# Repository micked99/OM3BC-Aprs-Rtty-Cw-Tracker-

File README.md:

# OM3BC-Aprs-Rtty-Cw-Tracker-
OM3BC Aprs-Rtty-Cw Tracker 
OM3BC tracker info
Some extended information about the OM3BC tracker found here: www.om3bc.com/docs/payload/payload_en

Some extended information about the OM3BC tracker found here: www.om3bc.com/docs/payload/payload_en
My aim of the Eagle files is to make an as simple to build, cheap and light tracker as possible, a fully assambled board should weigh in on about 1 - 1.3gram,
a fully assambled board with solar cells and antenna about 3.5gram

Im using 6 of the smallest avalible (19x39mm) solar cells in series to power the board, it makes it run from and to 15-19° solar angle depending on Gps used

After more then 25 launches over the years and probably more then 10 pcb revisions I have come to this final? design, the intention of this page is to ease the building and configuring the OM3BC APRS / RTTY / CW tracker.

The rar file below contains all files mentioned in this small writeup

There are two different firmware versions depending on what Gps module you intend to use:

fw7.5 should be used with Ublox Max modules, I have so far only tested the Max7q and Max7c both working well,
the low voltage "c" version getting a bit longer "runtime" due to its lower voltage demands, Max 6 & 8 should work just as well.

fw14 should be used with ATGM336 Gps which is a "new" cheap module that can be found for around $3 on Aliexpress,
there is no flightmode that needs to be set on this module, it have been tested to over 32000m at the time of this write up.

You will also find Eagle pcb files in the rar for two types of PIC ic footprints.

I have tested both the L version and LF version of the PIC but could not see any advantages using the low voltage (LF) version of the ic

All versions of the si4x6x I have tried have worked well, so far I have tested SI4060, 4463 and 4063.

THE MOST important setting to get reliable startup of the board is to enable the Watch Dog Timer (WDT) you set all as 1:s as in the below picture.
To do this you press the "Configuration:" in the PICkit3 before you program the board.

You can read about the fuses in the pic18f26k22.pdf (rar)

Schematic

Settings Im using:
MYC SA6BSS-9
DEVIATION 425
POUT 8 (pout 100 using 4060 // pout 8 = 25mW on a 4x63)
APRS on
HOLD 2
TAIL on 2
INTEMP yes REF 19199985
UBLOX on (=atgm336)
TTEXT RTTY 434.5/100b7n2 Temp:\W Gps:\B
UNPROTO APRS V wide0-0 // = to not use digipeaters, leave unchanged if you want to use digipeaters
RFRQ 434500000 // putting the rtty up in ism band

Im using Termite terminal to setup the board, this as well as well as the PICkit3 is in the rar, termite also supports macros so you dont have to enter every setting everytime you setup a new board.

When you configure the board you have to use a rs232 programmer, the only one so far that works reliably is this type, look for it on ebay or aliexpress,
should cost arround 3-5$, note the DC jack, electrolytic caps and LEDs
The voltage out from this is 5V, to reduce this you can put 2 diods in series on the VCC to lower the voltage to more reasonable levels, or preferably a 3.3V LDO.

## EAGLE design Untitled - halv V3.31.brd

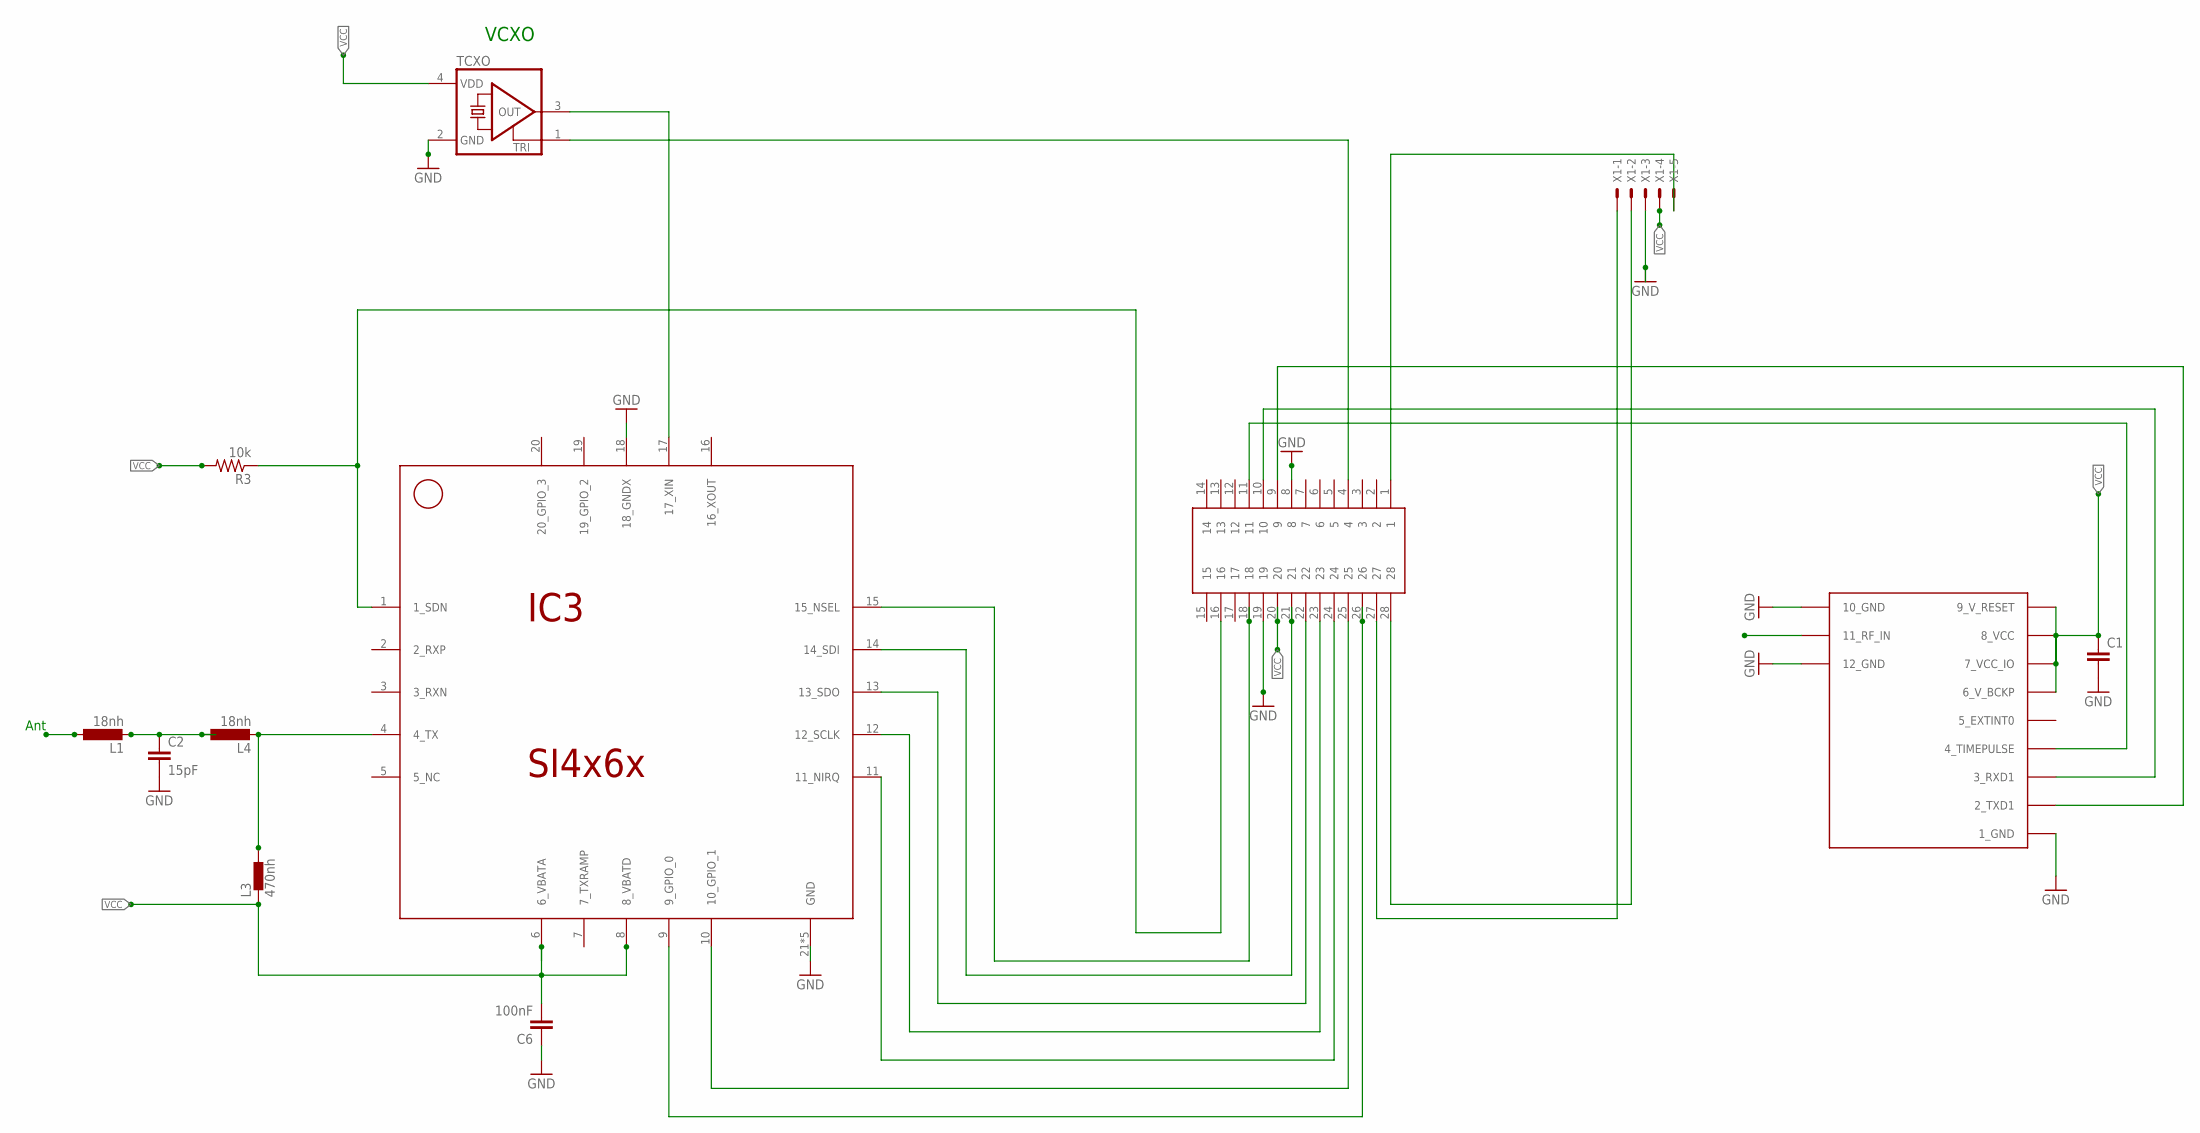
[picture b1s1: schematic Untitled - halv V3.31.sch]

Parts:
C1: CC0603; C0603
C2: 15pF; C0603K
C6: 100nF; C0402
IC3: SI4x6x; QFN-20
L1, L4: 18nh; L2012C
L3: 470nh; 0402
PIC-VERS3.3: SSOP28; SSOP28DB
R3: 10k; R0402
TCXO: CRYSTAL_3.2X2.5-TCXO
U$1: UBLOX_MAX
X1: 22-23-2051

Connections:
ANT: U$1.11_RF_IN
GND: C1.2, C2.2, C6.1, IC3.18 (18_GNDX), IC3.21 (GND), IC3.22 (GND), IC3.23 (GND), IC3.24 (GND), IC3.25 (GND), PIC-VERS3.3.8, PIC-VERS3.3.19, TCXO.2 (GND), U$1.1_GND, U$1.10_GND, U$1.12_GND, X1.3
unnamed: PIC-VERS3.3.1, X1.5
unnamed: PIC-VERS3.3.28, X1.2
unnamed: PIC-VERS3.3.27, X1.1
unnamed: IC3.9 (9_GPIO_0), PIC-VERS3.3.26
unnamed: IC3.10 (10_GPIO_1), PIC-VERS3.3.25
unnamed: IC3.11 (11_NIRQ), PIC-VERS3.3.24
unnamed: IC3.12 (12_SCLK), PIC-VERS3.3.23
unnamed: IC3.13 (13_SDO), PIC-VERS3.3.22
unnamed: IC3.14 (14_SDI), PIC-VERS3.3.21
unnamed: IC3.15 (15_NSEL), PIC-VERS3.3.18
unnamed: IC3.17 (17_XIN), TCXO.3 (OUT)
unnamed: IC3.4 (4_TX), L3.2, L4.2
unnamed: PIC-VERS3.3.4, TCXO.1 (TRI)
unnamed: PIC-VERS3.3.11, U$1.4_TIMEPULSE
unnamed: PIC-VERS3.3.10, U$1.3_RXD1
unnamed: C2.1, L1.2, L4.1
unnamed: PIC-VERS3.3.9, U$1.2_TXD1
RADIO_SDN: IC3.1 (1_SDN), PIC-VERS3.3.16, R3.1
VCC: C1.1, C6.2, IC3.6 (6_VBATA), IC3.8 (8_VBATD), L3.1, PIC-VERS3.3.20, R3.2, TCXO.4 (VDD), U$1.6_V_BCKP, U$1.7_VCC_IO, U$1.8_VCC, U$1.9_V_RESET, X1.4

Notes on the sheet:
VCXO
Ant

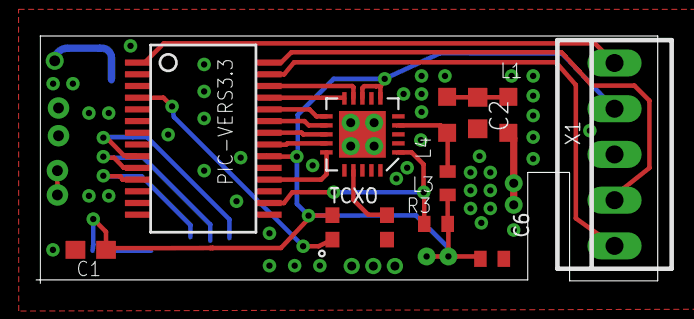
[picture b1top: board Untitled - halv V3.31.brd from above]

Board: 2 copper layers, 34.5 x 13.7 mm, 12 parts (1 on the bottom side), 20 nets.

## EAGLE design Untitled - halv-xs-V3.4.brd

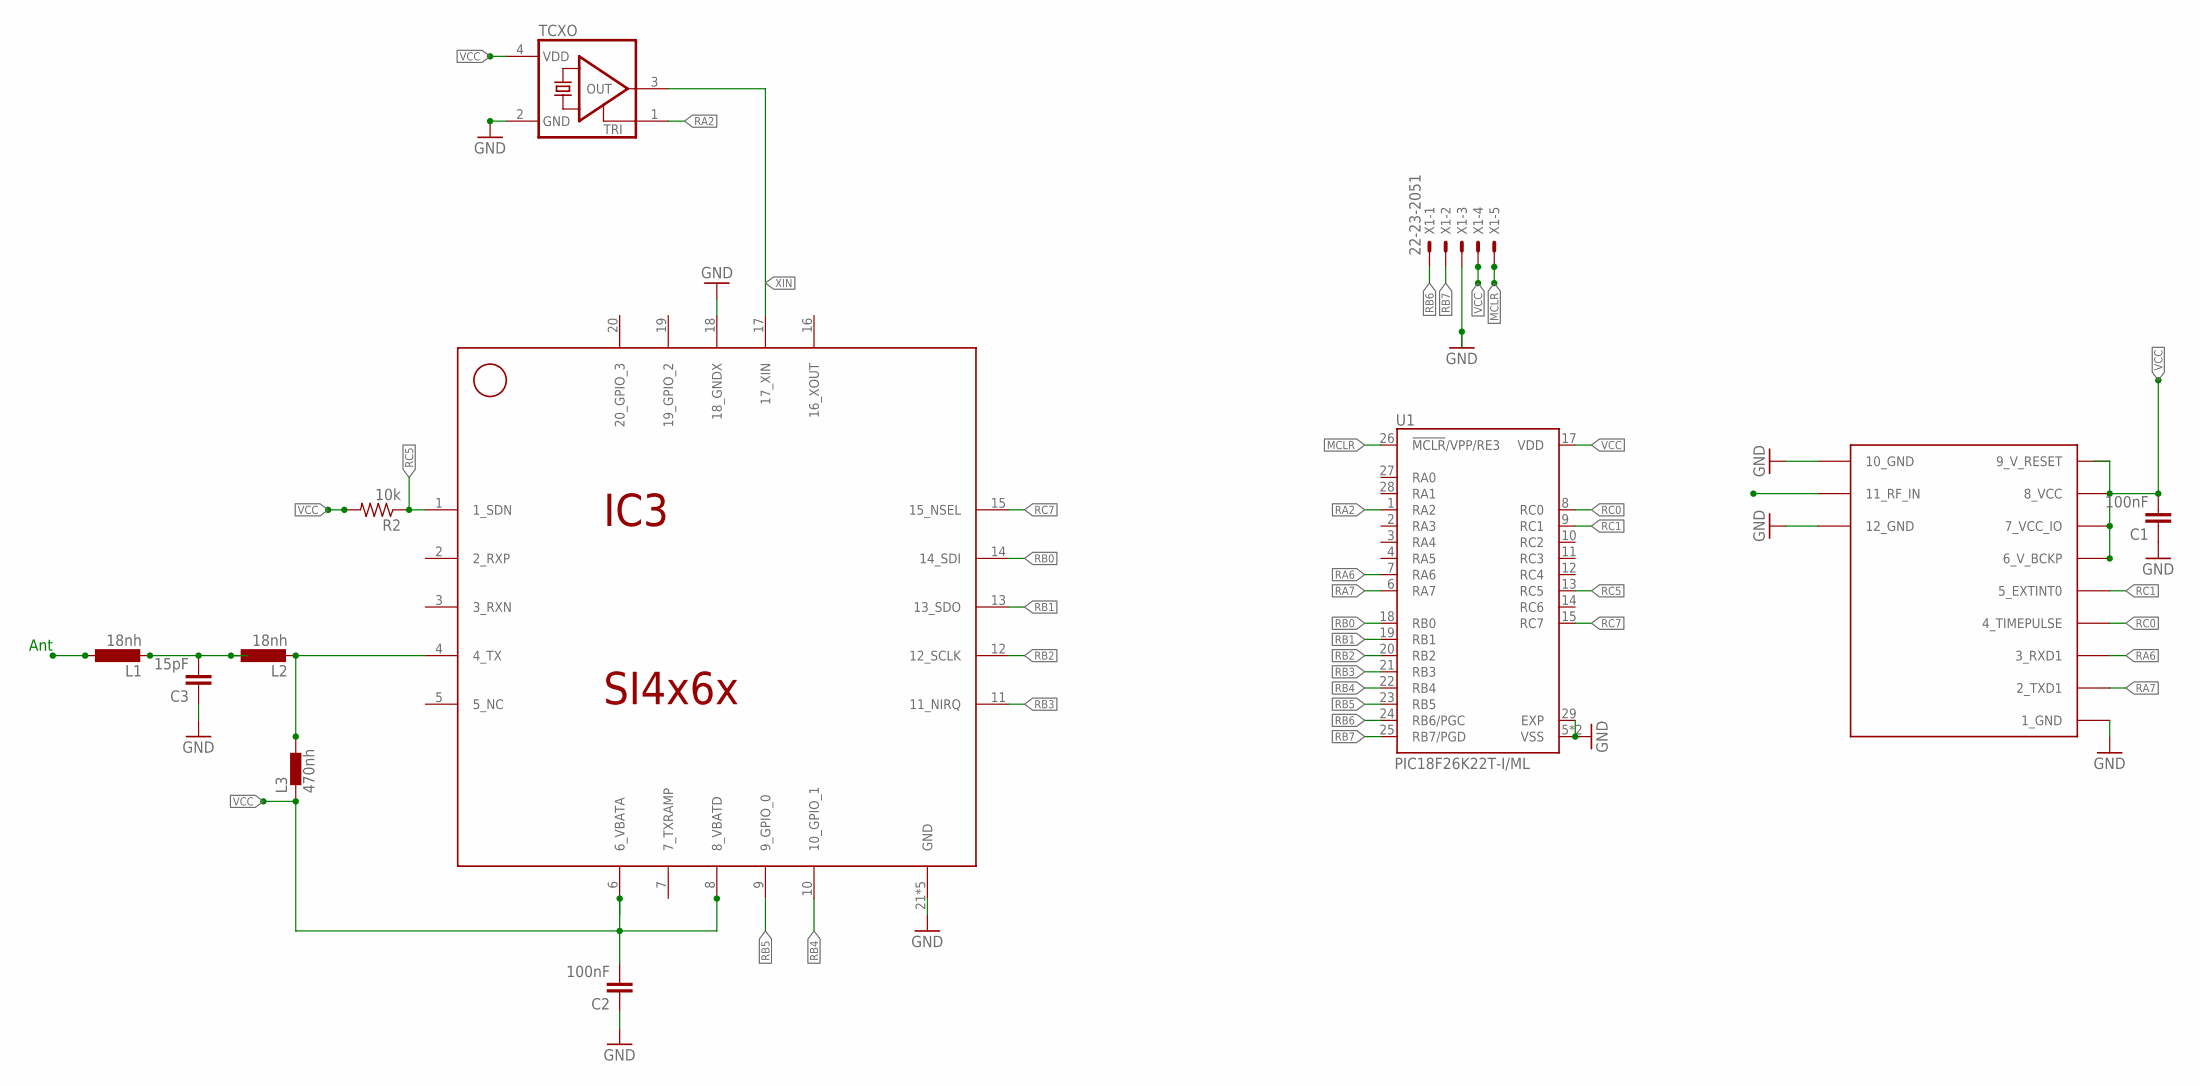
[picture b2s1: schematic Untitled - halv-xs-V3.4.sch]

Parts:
C1, C2: 100nF; C0402
C3: 15pF; C0402
IC3: SI4x6x; QFN-20
L1, L2: 18nh; L2012C
L3: 470nh; 0402
R2: 10k; R0402
TCXO: CRYSTAL_3.2X2.5-TCXO
U1: PIC18F26K22T-I/ML; QFN65P600X600X100-29N
U$1: UBLOX_MAX
X1: 22-23-2051

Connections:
ANT: U$1.11_RF_IN
GND: C1.1, C2.1, C3.1, IC3.18 (18_GNDX), IC3.21 (GND), IC3.22 (GND), IC3.23 (GND), IC3.24 (GND), IC3.25 (GND), TCXO.2 (GND), U1.5 (VSS), U1.16 (VSS), U1.29 (EXP), U$1.1_GND, U$1.10_GND, U$1.12_GND, X1.3
MCLR: U1.26 (!MCLR!/VPP/RE3), X1.5
unnamed: C3.2, L1.2, L2.1
RA2: TCXO.1 (TRI), U1.1 (RA2)
RA6: U1.7 (RA6), U$1.3_RXD1
RA7: U1.6 (RA7), U$1.2_TXD1
RB0: IC3.14 (14_SDI), U1.18 (RB0)
RB1: IC3.13 (13_SDO), U1.19 (RB1)
RB2: IC3.12 (12_SCLK), U1.20 (RB2)
RB3: IC3.11 (11_NIRQ), U1.21 (RB3)
RB4: IC3.10 (10_GPIO_1), U1.22 (RB4)
RB5: IC3.9 (9_GPIO_0), U1.23 (RB5)
RB6: U1.24 (RB6/PGC), X1.1
RB7: U1.25 (RB7/PGD), X1.2
RC0: U1.8 (RC0), U$1.4_TIMEPULSE
RC1: U1.9 (RC1), U$1.5_EXTINT0
RC5: IC3.1 (1_SDN), R2.1, U1.13 (RC5)
RC7: IC3.15 (15_NSEL), U1.15 (RC7)
TX: IC3.4 (4_TX), L2.2, L3.2
VCC: C1.2, C2.2, IC3.6 (6_VBATA), IC3.8 (8_VBATD), L3.1, R2.2, TCXO.4 (VDD), U1.17 (VDD), U$1.6_V_BCKP, U$1.7_VCC_IO, U$1.8_VCC, U$1.9_V_RESET, X1.4
XIN: IC3.17 (17_XIN), TCXO.3 (OUT)

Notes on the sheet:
Ant

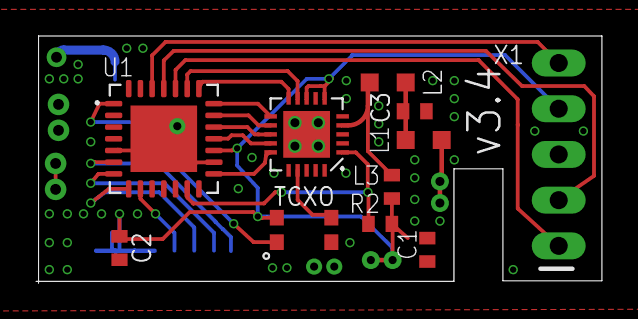
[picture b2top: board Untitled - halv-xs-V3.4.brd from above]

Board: 2 copper layers, 31.4 x 13.7 mm, 12 parts (1 on the bottom side), 21 nets.
